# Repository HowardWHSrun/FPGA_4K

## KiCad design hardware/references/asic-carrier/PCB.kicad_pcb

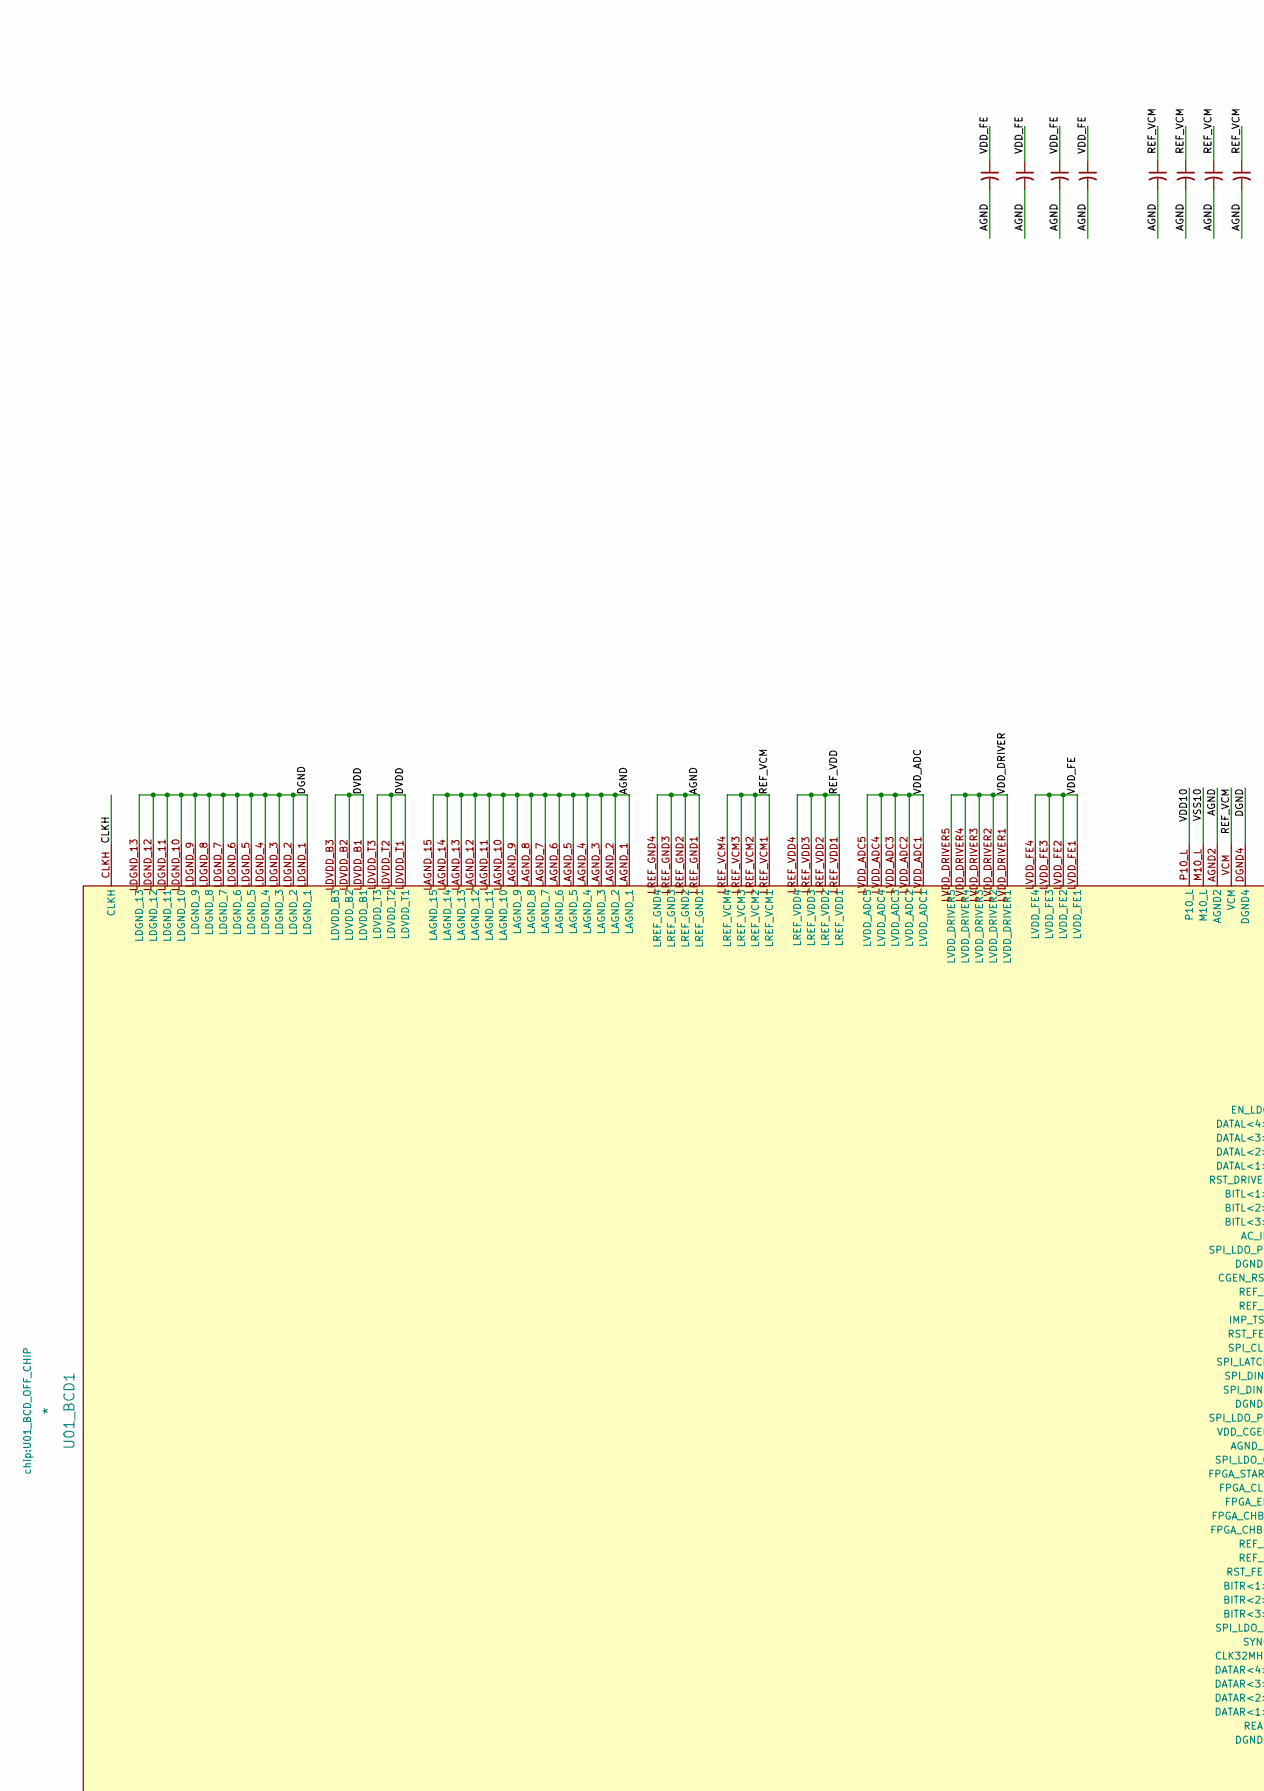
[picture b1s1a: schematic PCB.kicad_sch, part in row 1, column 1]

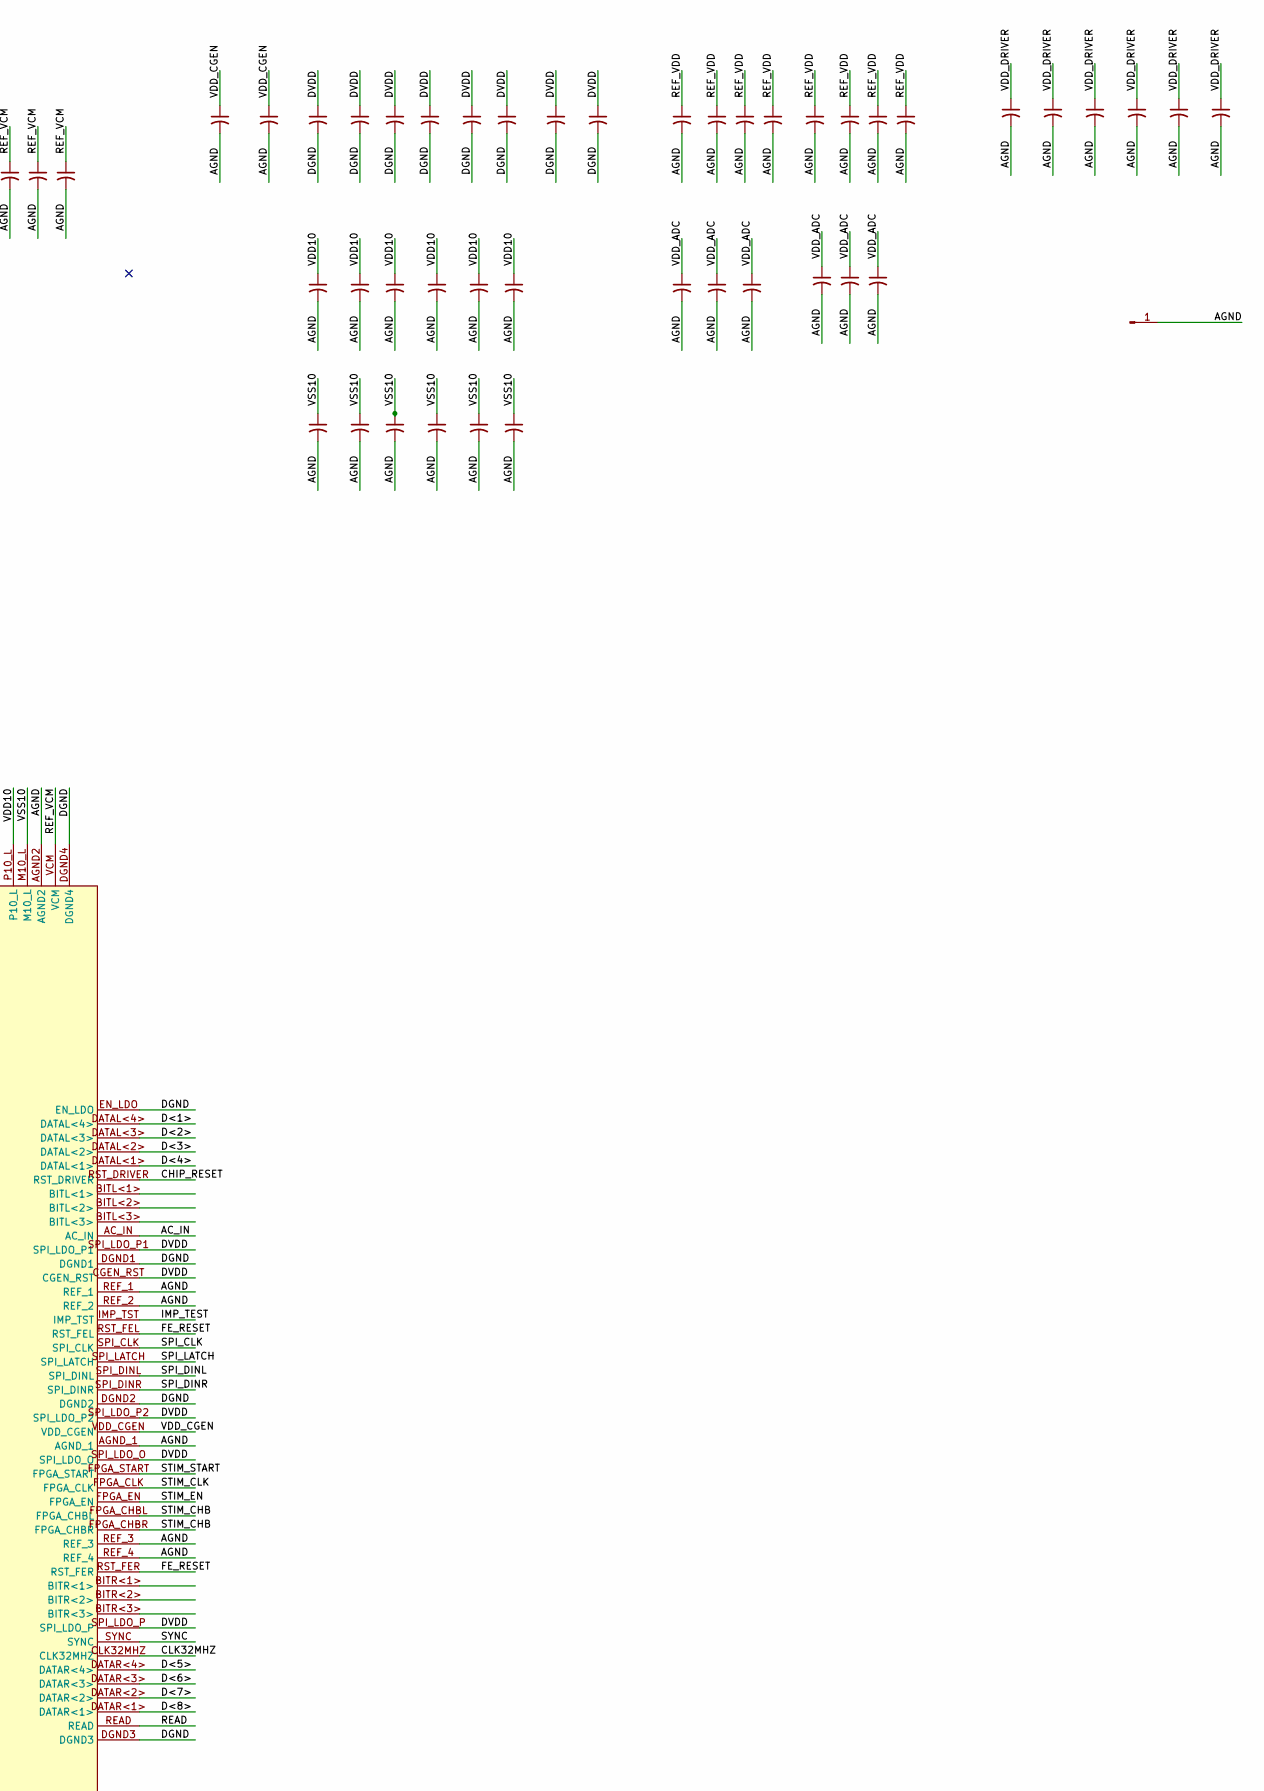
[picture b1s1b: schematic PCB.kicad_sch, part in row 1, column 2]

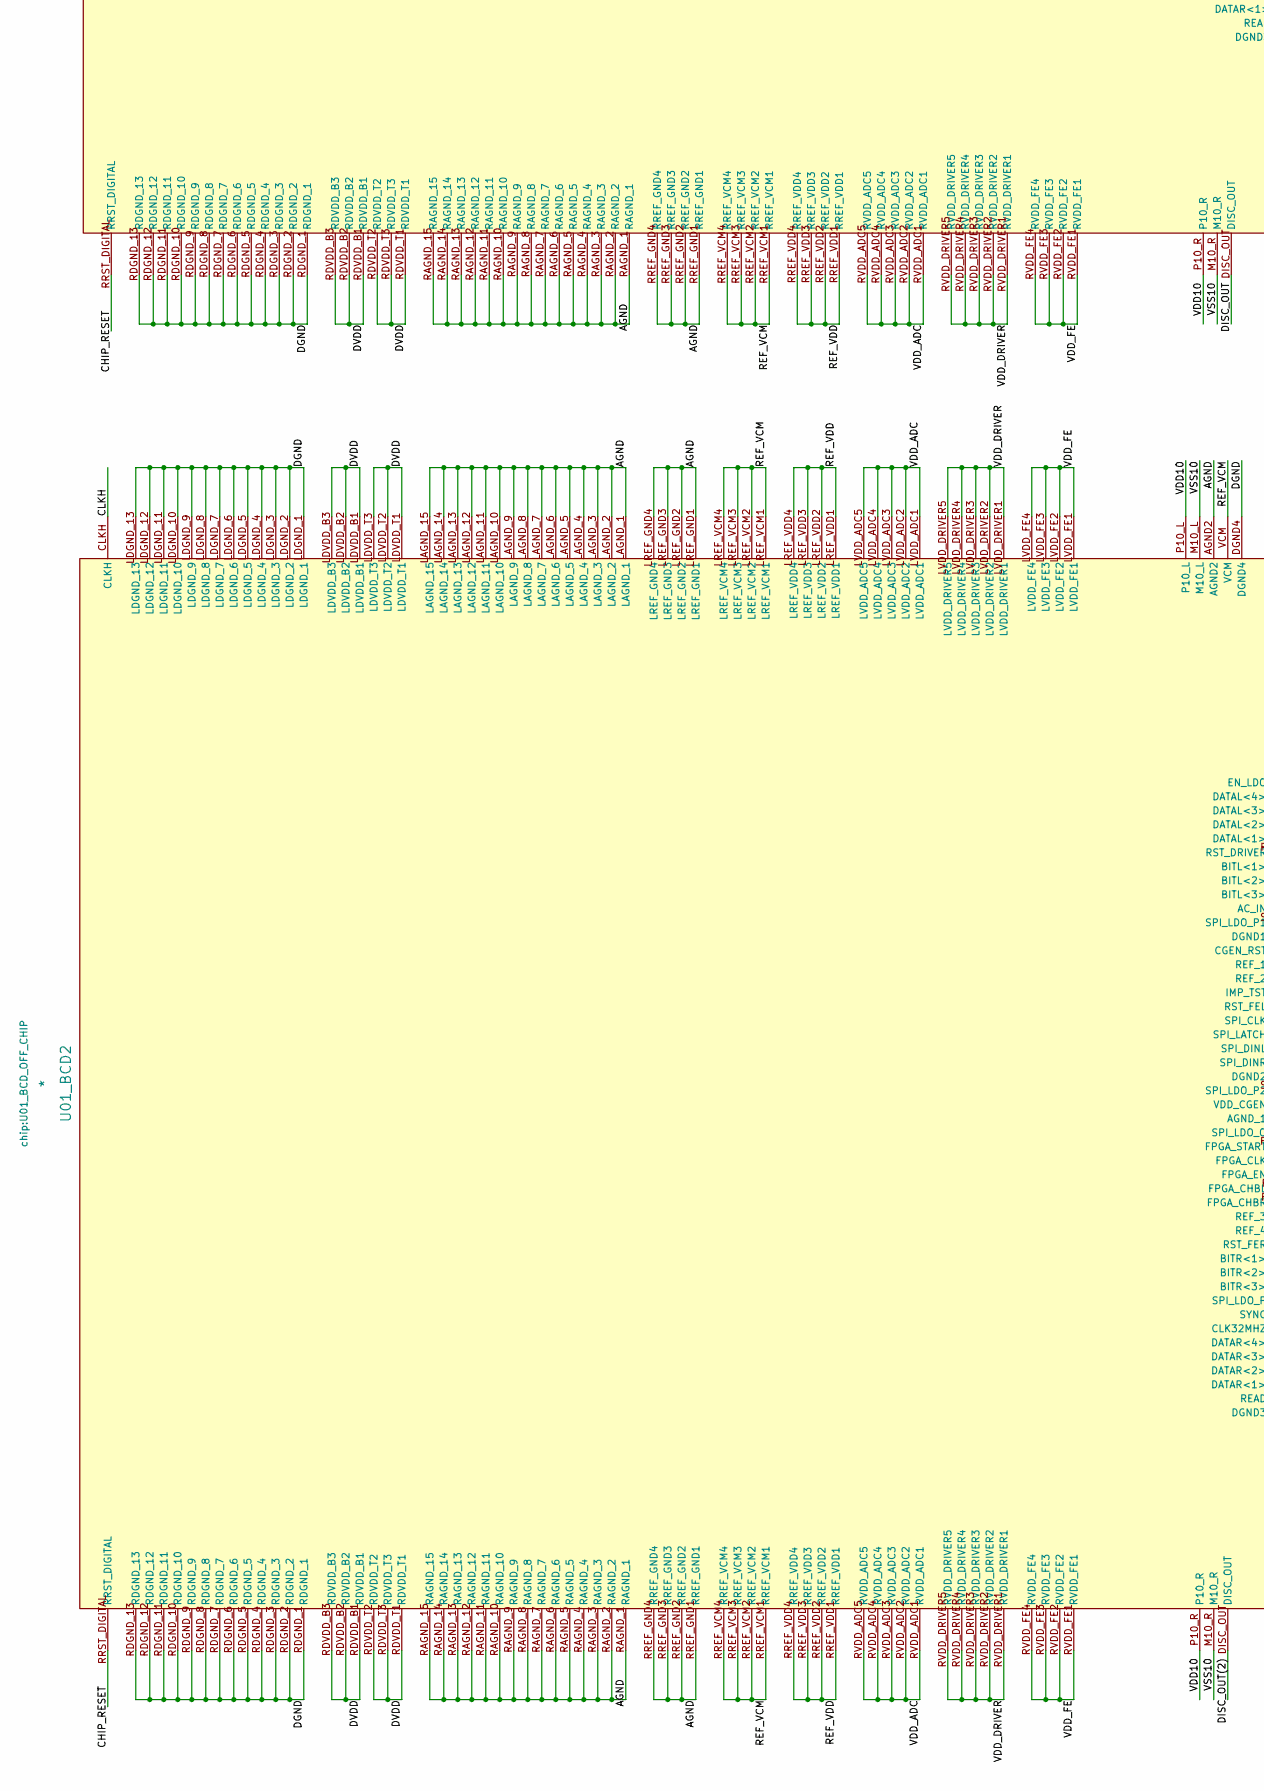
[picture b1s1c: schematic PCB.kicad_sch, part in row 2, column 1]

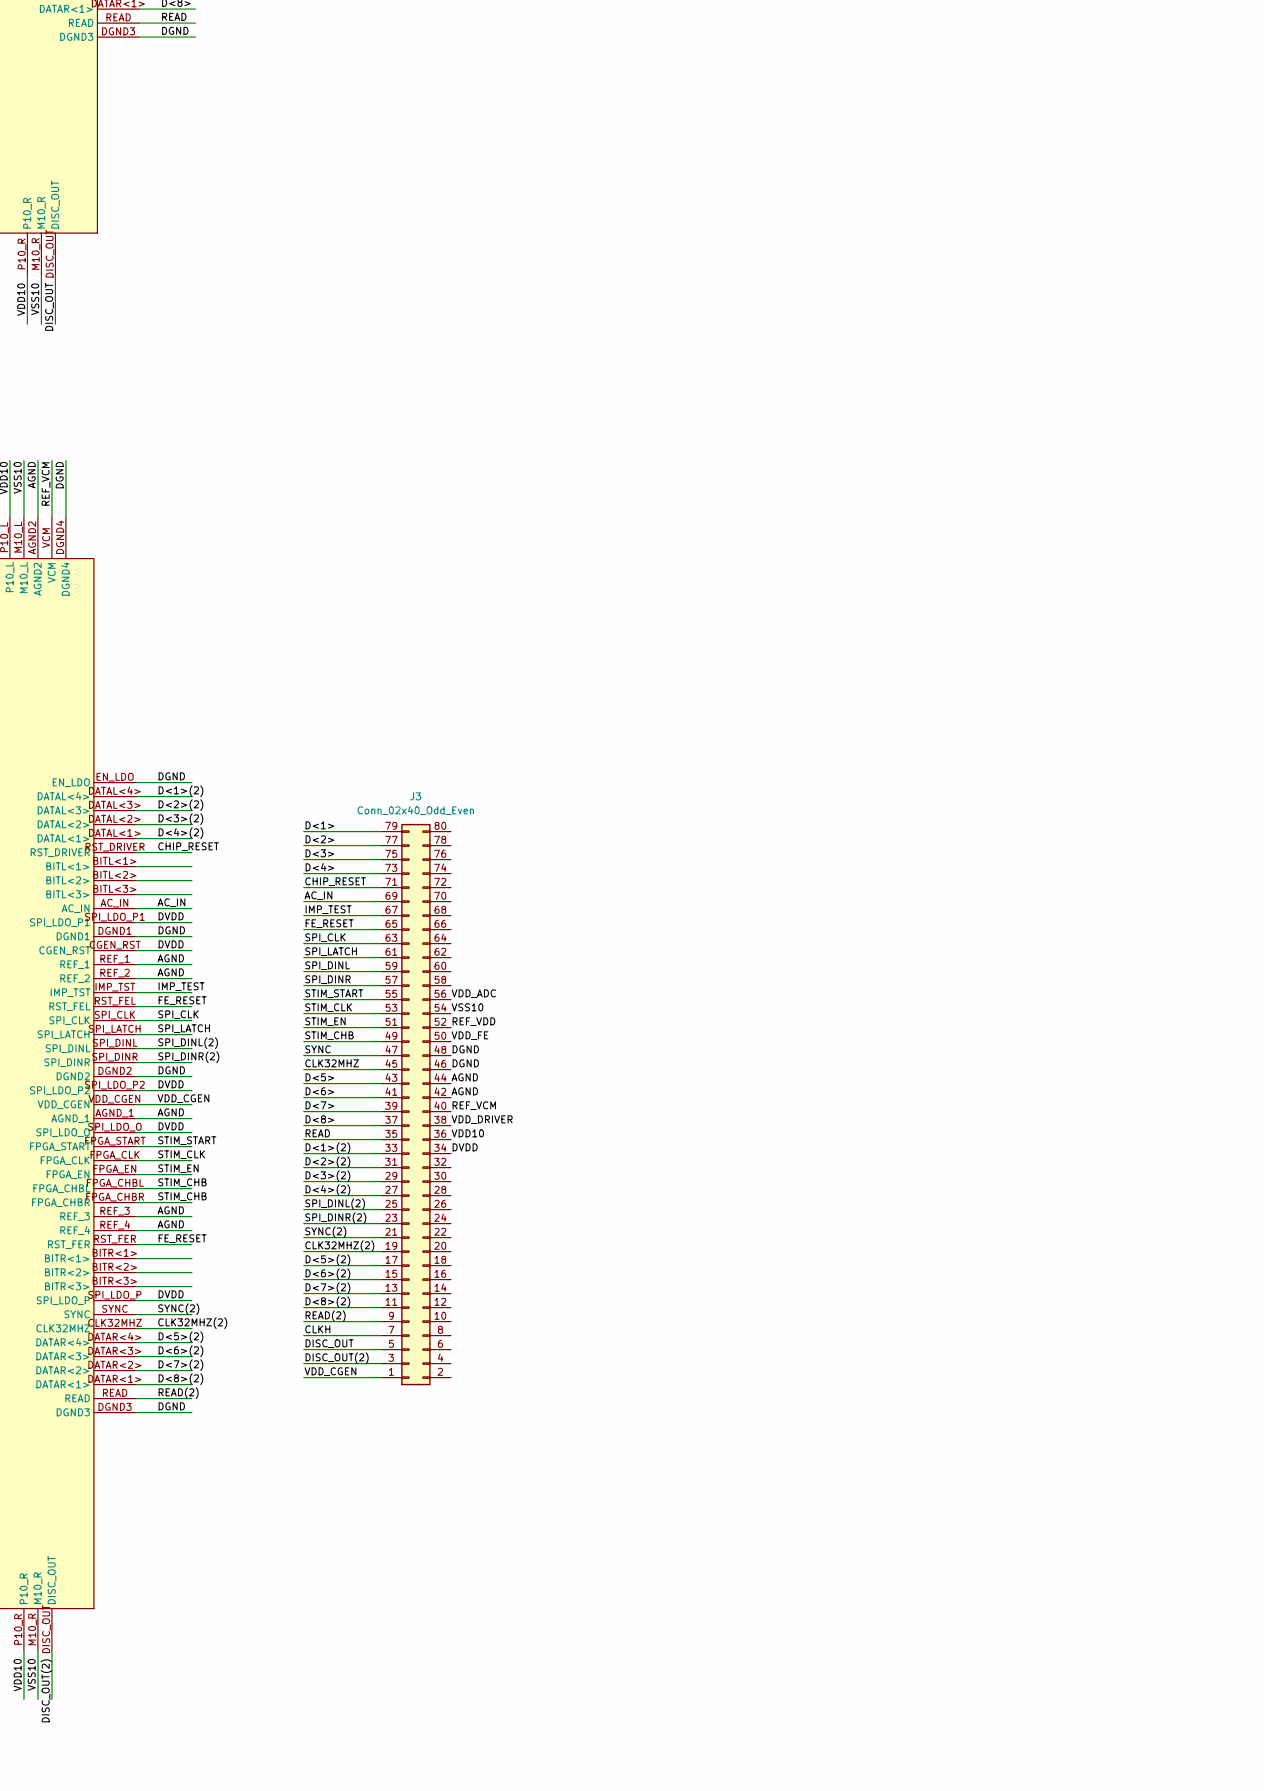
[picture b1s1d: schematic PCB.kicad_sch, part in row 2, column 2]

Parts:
C1, C2, C3, C4, C5, C6, C7, C8, C9, C10, C11, C12, C13, C14, C15, C16, C17, C18, C19, C20, C21, C22, C23, C24, C25, C26, C27, C28, C29, C30, C31, C32, C33, C34, C35, C36, C37, C38, C39, C40, C41, C42, C43, C44, C45, C46, C47, C48, C49, C50: C_Small_US; C_0201_0603Metric
J1: Conn_01x01_Pin; PinHeader_1x01_P1.00mm_Horizontal
J3: Conn_02x40_Odd_Even; Hirose_DF40C-80DS-0.4V_2x40_P0.4mm
U01_BCD1, U01_BCD2: *; U01_BCD_OFF_CHIP

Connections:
/AC_IN: J3.69, U01_BCD1.AC_IN, U01_BCD2.AC_IN
/AGND: C1.2, C2.2, C3.2, C4.2, C5.2, C6.2, C15.2, C16.2, C17.2, C18.2, C19.2, C20.2, C21.2, C22.2, C23.2, C24.2, C25.2, C26.2, C27.2, C28.2, C29.2, C30.2, C31.2, C32.2, C33.2, C34.2, C35.2, C36.2, C37.2, C38.2, C39.2, C40.2, C41.2, C42.2, C43.2, C44.2, C45.2, C46.2, C47.2, C48.2, C49.2, C50.2, J1.1 (Pin_1_1), J3.42, J3.44, U01_BCD1.AGND2, U01_BCD1.AGND_1, U01_BCD1.LAGND_1, U01_BCD1.LAGND_2, U01_BCD1.LAGND_3, U01_BCD1.LAGND_4, U01_BCD1.LAGND_5, U01_BCD1.LAGND_6, U01_BCD1.LAGND_7, U01_BCD1.LAGND_8, U01_BCD1.LAGND_9, U01_BCD1.LAGND_10, U01_BCD1.LAGND_11, U01_BCD1.LAGND_12, U01_BCD1.LAGND_13, U01_BCD1.LAGND_14, U01_BCD1.LAGND_15, U01_BCD1.LREF_GND1, U01_BCD1.LREF_GND2, U01_BCD1.LREF_GND3, U01_BCD1.LREF_GND4, U01_BCD1.RAGND_1, U01_BCD1.RAGND_2, U01_BCD1.RAGND_3, U01_BCD1.RAGND_4, U01_BCD1.RAGND_5, U01_BCD1.RAGND_6, U01_BCD1.RAGND_7, U01_BCD1.RAGND_8, U01_BCD1.RAGND_9, U01_BCD1.RAGND_10, U01_BCD1.RAGND_11, U01_BCD1.RAGND_12, U01_BCD1.RAGND_13, U01_BCD1.RAGND_14, U01_BCD1.RAGND_15, U01_BCD1.REF_1, U01_BCD1.REF_2, U01_BCD1.REF_3, U01_BCD1.REF_4, U01_BCD1.RREF_GND1, U01_BCD1.RREF_GND2, U01_BCD1.RREF_GND3, U01_BCD1.RREF_GND4, U01_BCD2.AGND2, U01_BCD2.AGND_1, U01_BCD2.LAGND_1, U01_BCD2.LAGND_2, U01_BCD2.LAGND_3, U01_BCD2.LAGND_4, U01_BCD2.LAGND_5, U01_BCD2.LAGND_6, U01_BCD2.LAGND_7, U01_BCD2.LAGND_8, U01_BCD2.LAGND_9, U01_BCD2.LAGND_10, U01_BCD2.LAGND_11, U01_BCD2.LAGND_12, U01_BCD2.LAGND_13, U01_BCD2.LAGND_14, U01_BCD2.LAGND_15, U01_BCD2.LREF_GND1, U01_BCD2.LREF_GND2, U01_BCD2.LREF_GND3, U01_BCD2.LREF_GND4, U01_BCD2.RAGND_1, U01_BCD2.RAGND_2, U01_BCD2.RAGND_3, U01_BCD2.RAGND_4, U01_BCD2.RAGND_5, U01_BCD2.RAGND_6, U01_BCD2.RAGND_7, U01_BCD2.RAGND_8, U01_BCD2.RAGND_9, U01_BCD2.RAGND_10, U01_BCD2.RAGND_11, U01_BCD2.RAGND_12, U01_BCD2.RAGND_13, U01_BCD2.RAGND_14, U01_BCD2.RAGND_15, U01_BCD2.REF_1, U01_BCD2.REF_2, U01_BCD2.REF_3, U01_BCD2.REF_4, U01_BCD2.RREF_GND1, U01_BCD2.RREF_GND2, U01_BCD2.RREF_GND3, U01_BCD2.RREF_GND4
/CHIP_RESET: J3.71, U01_BCD1.RRST_DIGITAL, U01_BCD1.RST_DRIVER, U01_BCD2.RRST_DIGITAL, U01_BCD2.RST_DRIVER
/CLK32MHZ: J3.45, U01_BCD1.CLK32MHZ
/CLK32MHZ(2): J3.19, U01_BCD2.CLK32MHZ
/CLKH: J3.7, U01_BCD1.CLKH, U01_BCD2.CLKH
/D<1>: J3.79, U01_BCD1.DATAL<4>
/D<1>(2): J3.33, U01_BCD2.DATAL<4>
/D<2>: J3.77, U01_BCD1.DATAL<3>
/D<2>(2): J3.31, U01_BCD2.DATAL<3>
/D<3>: J3.75, U01_BCD1.DATAL<2>
/D<3>(2): J3.29, U01_BCD2.DATAL<2>
/D<4>: J3.73, U01_BCD1.DATAL<1>
/D<4>(2): J3.27, U01_BCD2.DATAL<1>
/D<5>: J3.43, U01_BCD1.DATAR<4>
/D<5>(2): J3.17, U01_BCD2.DATAR<4>
/D<6>: J3.41, U01_BCD1.DATAR<3>
/D<6>(2): J3.15, U01_BCD2.DATAR<3>
/D<7>: J3.39, U01_BCD1.DATAR<2>
/D<7>(2): J3.13, U01_BCD2.DATAR<2>
/D<8>: J3.37, U01_BCD1.DATAR<1>
/D<8>(2): J3.11, U01_BCD2.DATAR<1>
/DGND: C7.2, C8.2, C9.2, C10.2, C11.2, C12.2, C13.2, C14.2, J3.46, J3.48, U01_BCD1.DGND1, U01_BCD1.DGND2, U01_BCD1.DGND3, U01_BCD1.DGND4, U01_BCD1.EN_LDO, U01_BCD1.LDGND_1, U01_BCD1.LDGND_2, U01_BCD1.LDGND_3, U01_BCD1.LDGND_4, U01_BCD1.LDGND_5, U01_BCD1.LDGND_6, U01_BCD1.LDGND_7, U01_BCD1.LDGND_8, U01_BCD1.LDGND_9, U01_BCD1.LDGND_10, U01_BCD1.LDGND_11, U01_BCD1.LDGND_12, U01_BCD1.LDGND_13, U01_BCD1.RDGND_1, U01_BCD1.RDGND_2, U01_BCD1.RDGND_3, U01_BCD1.RDGND_4, U01_BCD1.RDGND_5, U01_BCD1.RDGND_6, U01_BCD1.RDGND_7, U01_BCD1.RDGND_8, U01_BCD1.RDGND_9, U01_BCD1.RDGND_10, U01_BCD1.RDGND_11, U01_BCD1.RDGND_12, U01_BCD1.RDGND_13, U01_BCD2.DGND1, U01_BCD2.DGND2, U01_BCD2.DGND3, U01_BCD2.DGND4, U01_BCD2.EN_LDO, U01_BCD2.LDGND_1, U01_BCD2.LDGND_2, U01_BCD2.LDGND_3, U01_BCD2.LDGND_4, U01_BCD2.LDGND_5, U01_BCD2.LDGND_6, U01_BCD2.LDGND_7, U01_BCD2.LDGND_8, U01_BCD2.LDGND_9, U01_BCD2.LDGND_10, U01_BCD2.LDGND_11, U01_BCD2.LDGND_12, U01_BCD2.LDGND_13, U01_BCD2.RDGND_1, U01_BCD2.RDGND_2, U01_BCD2.RDGND_3, U01_BCD2.RDGND_4, U01_BCD2.RDGND_5, U01_BCD2.RDGND_6, U01_BCD2.RDGND_7, U01_BCD2.RDGND_8, U01_BCD2.RDGND_9, U01_BCD2.RDGND_10, U01_BCD2.RDGND_11, U01_BCD2.RDGND_12, U01_BCD2.RDGND_13
/DISC_OUT: J3.5, U01_BCD1.DISC_OUT
/DISC_OUT(2): J3.3, U01_BCD2.DISC_OUT
/DVDD: C7.1, C8.1, C9.1, C10.1, C11.1, C12.1, C13.1, C14.1, J3.34, U01_BCD1.CGEN_RST, U01_BCD1.LDVDD_B1, U01_BCD1.LDVDD_B2, U01_BCD1.LDVDD_B3, U01_BCD1.LDVDD_T1, U01_BCD1.LDVDD_T2, U01_BCD1.LDVDD_T3, U01_BCD1.RDVDD_B1, U01_BCD1.RDVDD_B2, U01_BCD1.RDVDD_B3, U01_BCD1.RDVDD_T1, U01_BCD1.RDVDD_T2, U01_BCD1.RDVDD_T3, U01_BCD1.SPI_LDO_O, U01_BCD1.SPI_LDO_P, U01_BCD1.SPI_LDO_P1, U01_BCD1.SPI_LDO_P2, U01_BCD2.CGEN_RST, U01_BCD2.LDVDD_B1, U01_BCD2.LDVDD_B2, U01_BCD2.LDVDD_B3, U01_BCD2.LDVDD_T1, U01_BCD2.LDVDD_T2, U01_BCD2.LDVDD_T3, U01_BCD2.RDVDD_B1, U01_BCD2.RDVDD_B2, U01_BCD2.RDVDD_B3, U01_BCD2.RDVDD_T1, U01_BCD2.RDVDD_T2, U01_BCD2.RDVDD_T3, U01_BCD2.SPI_LDO_O, U01_BCD2.SPI_LDO_P, U01_BCD2.SPI_LDO_P1, U01_BCD2.SPI_LDO_P2
/FE_RESET: J3.65, U01_BCD1.RST_FEL, U01_BCD1.RST_FER, U01_BCD2.RST_FEL, U01_BCD2.RST_FER
/IMP_TEST: J3.67, U01_BCD1.IMP_TST, U01_BCD2.IMP_TST
/READ: J3.35, U01_BCD1.READ
/READ(2): J3.9, U01_BCD2.READ
/REF_VCM: C5.1, C46.1, C47.1, C49.1, J3.40, U01_BCD1.LREF_VCM1, U01_BCD1.LREF_VCM2, U01_BCD1.LREF_VCM3, U01_BCD1.LREF_VCM4, U01_BCD1.RREF_VCM1, U01_BCD1.RREF_VCM2, U01_BCD1.RREF_VCM3, U01_BCD1.RREF_VCM4, U01_BCD1.VCM, U01_BCD2.LREF_VCM1, U01_BCD2.LREF_VCM2, U01_BCD2.LREF_VCM3, U01_BCD2.LREF_VCM4, U01_BCD2.RREF_VCM1, U01_BCD2.RREF_VCM2, U01_BCD2.RREF_VCM3, U01_BCD2.RREF_VCM4, U01_BCD2.VCM
/REF_VDD: C2.1, C27.1, C28.1, C29.1, C30.1, C31.1, C32.1, C33.1, J3.52, U01_BCD1.LREF_VDD1, U01_BCD1.LREF_VDD2, U01_BCD1.LREF_VDD3, U01_BCD1.LREF_VDD4, U01_BCD1.RREF_VDD1, U01_BCD1.RREF_VDD2, U01_BCD1.RREF_VDD3, U01_BCD1.RREF_VDD4, U01_BCD2.LREF_VDD1, U01_BCD2.LREF_VDD2, U01_BCD2.LREF_VDD3, U01_BCD2.LREF_VDD4, U01_BCD2.RREF_VDD1, U01_BCD2.RREF_VDD2, U01_BCD2.RREF_VDD3, U01_BCD2.RREF_VDD4
/SPI_CLK: J3.63, U01_BCD1.SPI_CLK, U01_BCD2.SPI_CLK
/SPI_DINL: J3.59, U01_BCD1.SPI_DINL
/SPI_DINL(2): J3.25, U01_BCD2.SPI_DINL
/SPI_DINR: J3.57, U01_BCD1.SPI_DINR
/SPI_DINR(2): J3.23, U01_BCD2.SPI_DINR
/SPI_LATCH: J3.61, U01_BCD1.SPI_LATCH, U01_BCD2.SPI_LATCH
/STIM_CHB: J3.49, U01_BCD1.FPGA_CHBL, U01_BCD1.FPGA_CHBR, U01_BCD2.FPGA_CHBL, U01_BCD2.FPGA_CHBR
/STIM_CLK: J3.53, U01_BCD1.FPGA_CLK, U01_BCD2.FPGA_CLK
/STIM_EN: J3.51, U01_BCD1.FPGA_EN, U01_BCD2.FPGA_EN
/STIM_START: J3.55, U01_BCD1.FPGA_START, U01_BCD2.FPGA_START
/SYNC: J3.47, U01_BCD1.SYNC
/SYNC(2): J3.21, U01_BCD2.SYNC
/VDD10: C15.1, C16.1, C17.1, C18.1, C19.1, C20.1, J3.36, U01_BCD1.P10_L, U01_BCD1.P10_R, U01_BCD2.P10_L, U01_BCD2.P10_R
/VDD_ADC: C1.1, C34.1, C35.1, C36.1, C37.1, C38.1, J3.56, U01_BCD1.LVDD_ADC1, U01_BCD1.LVDD_ADC2, U01_BCD1.LVDD_ADC3, U01_BCD1.LVDD_ADC4, U01_BCD1.LVDD_ADC5, U01_BCD1.RVDD_ADC1, U01_BCD1.RVDD_ADC2, U01_BCD1.RVDD_ADC3, U01_BCD1.RVDD_ADC4, U01_BCD1.RVDD_ADC5, U01_BCD2.LVDD_ADC1, U01_BCD2.LVDD_ADC2, U01_BCD2.LVDD_ADC3, U01_BCD2.LVDD_ADC4, U01_BCD2.LVDD_ADC5, U01_BCD2.RVDD_ADC1, U01_BCD2.RVDD_ADC2, U01_BCD2.RVDD_ADC3, U01_BCD2.RVDD_ADC4, U01_BCD2.RVDD_ADC5
/VDD_CGEN: C6.1, C50.1, J3.1, U01_BCD1.VDD_CGEN, U01_BCD2.VDD_CGEN
/VDD_DRIVER: C3.1, C39.1, C40.1, C41.1, C42.1, C43.1, J3.38, U01_BCD1.LVDD_DRIVER1, U01_BCD1.LVDD_DRIVER2, U01_BCD1.LVDD_DRIVER3, U01_BCD1.LVDD_DRIVER4, U01_BCD1.LVDD_DRIVER5, U01_BCD1.RVDD_DRIVER1, U01_BCD1.RVDD_DRIVER2, U01_BCD1.RVDD_DRIVER3, U01_BCD1.RVDD_DRIVER4, U01_BCD1.RVDD_DRIVER5, U01_BCD2.LVDD_DRIVER1, U01_BCD2.LVDD_DRIVER2, U01_BCD2.LVDD_DRIVER3, U01_BCD2.LVDD_DRIVER4, U01_BCD2.LVDD_DRIVER5, U01_BCD2.RVDD_DRIVER1, U01_BCD2.RVDD_DRIVER2, U01_BCD2.RVDD_DRIVER3, U01_BCD2.RVDD_DRIVER4, U01_BCD2.RVDD_DRIVER5
/VDD_FE: C4.1, C44.1, C45.1, C48.1, J3.50, U01_BCD1.LVDD_FE1, U01_BCD1.LVDD_FE2, U01_BCD1.LVDD_FE3, U01_BCD1.LVDD_FE4, U01_BCD1.RVDD_FE1, U01_BCD1.RVDD_FE2, U01_BCD1.RVDD_FE3, U01_BCD1.RVDD_FE4, U01_BCD2.LVDD_FE1, U01_BCD2.LVDD_FE2, U01_BCD2.LVDD_FE3, U01_BCD2.LVDD_FE4, U01_BCD2.RVDD_FE1, U01_BCD2.RVDD_FE2, U01_BCD2.RVDD_FE3, U01_BCD2.RVDD_FE4
/VSS10: C21.1, C22.1, C23.1, C24.1, C25.1, C26.1, J3.54, U01_BCD1.M10_L, U01_BCD1.M10_R, U01_BCD2.M10_L, U01_BCD2.M10_R

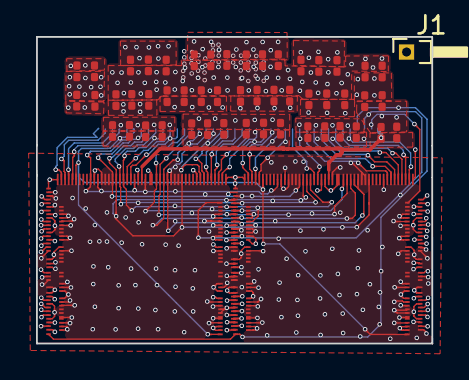
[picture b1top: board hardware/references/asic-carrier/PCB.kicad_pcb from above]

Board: 10 copper layers, 22.0 x 17.0 mm, 54 parts (1 on the bottom side), 50 nets.

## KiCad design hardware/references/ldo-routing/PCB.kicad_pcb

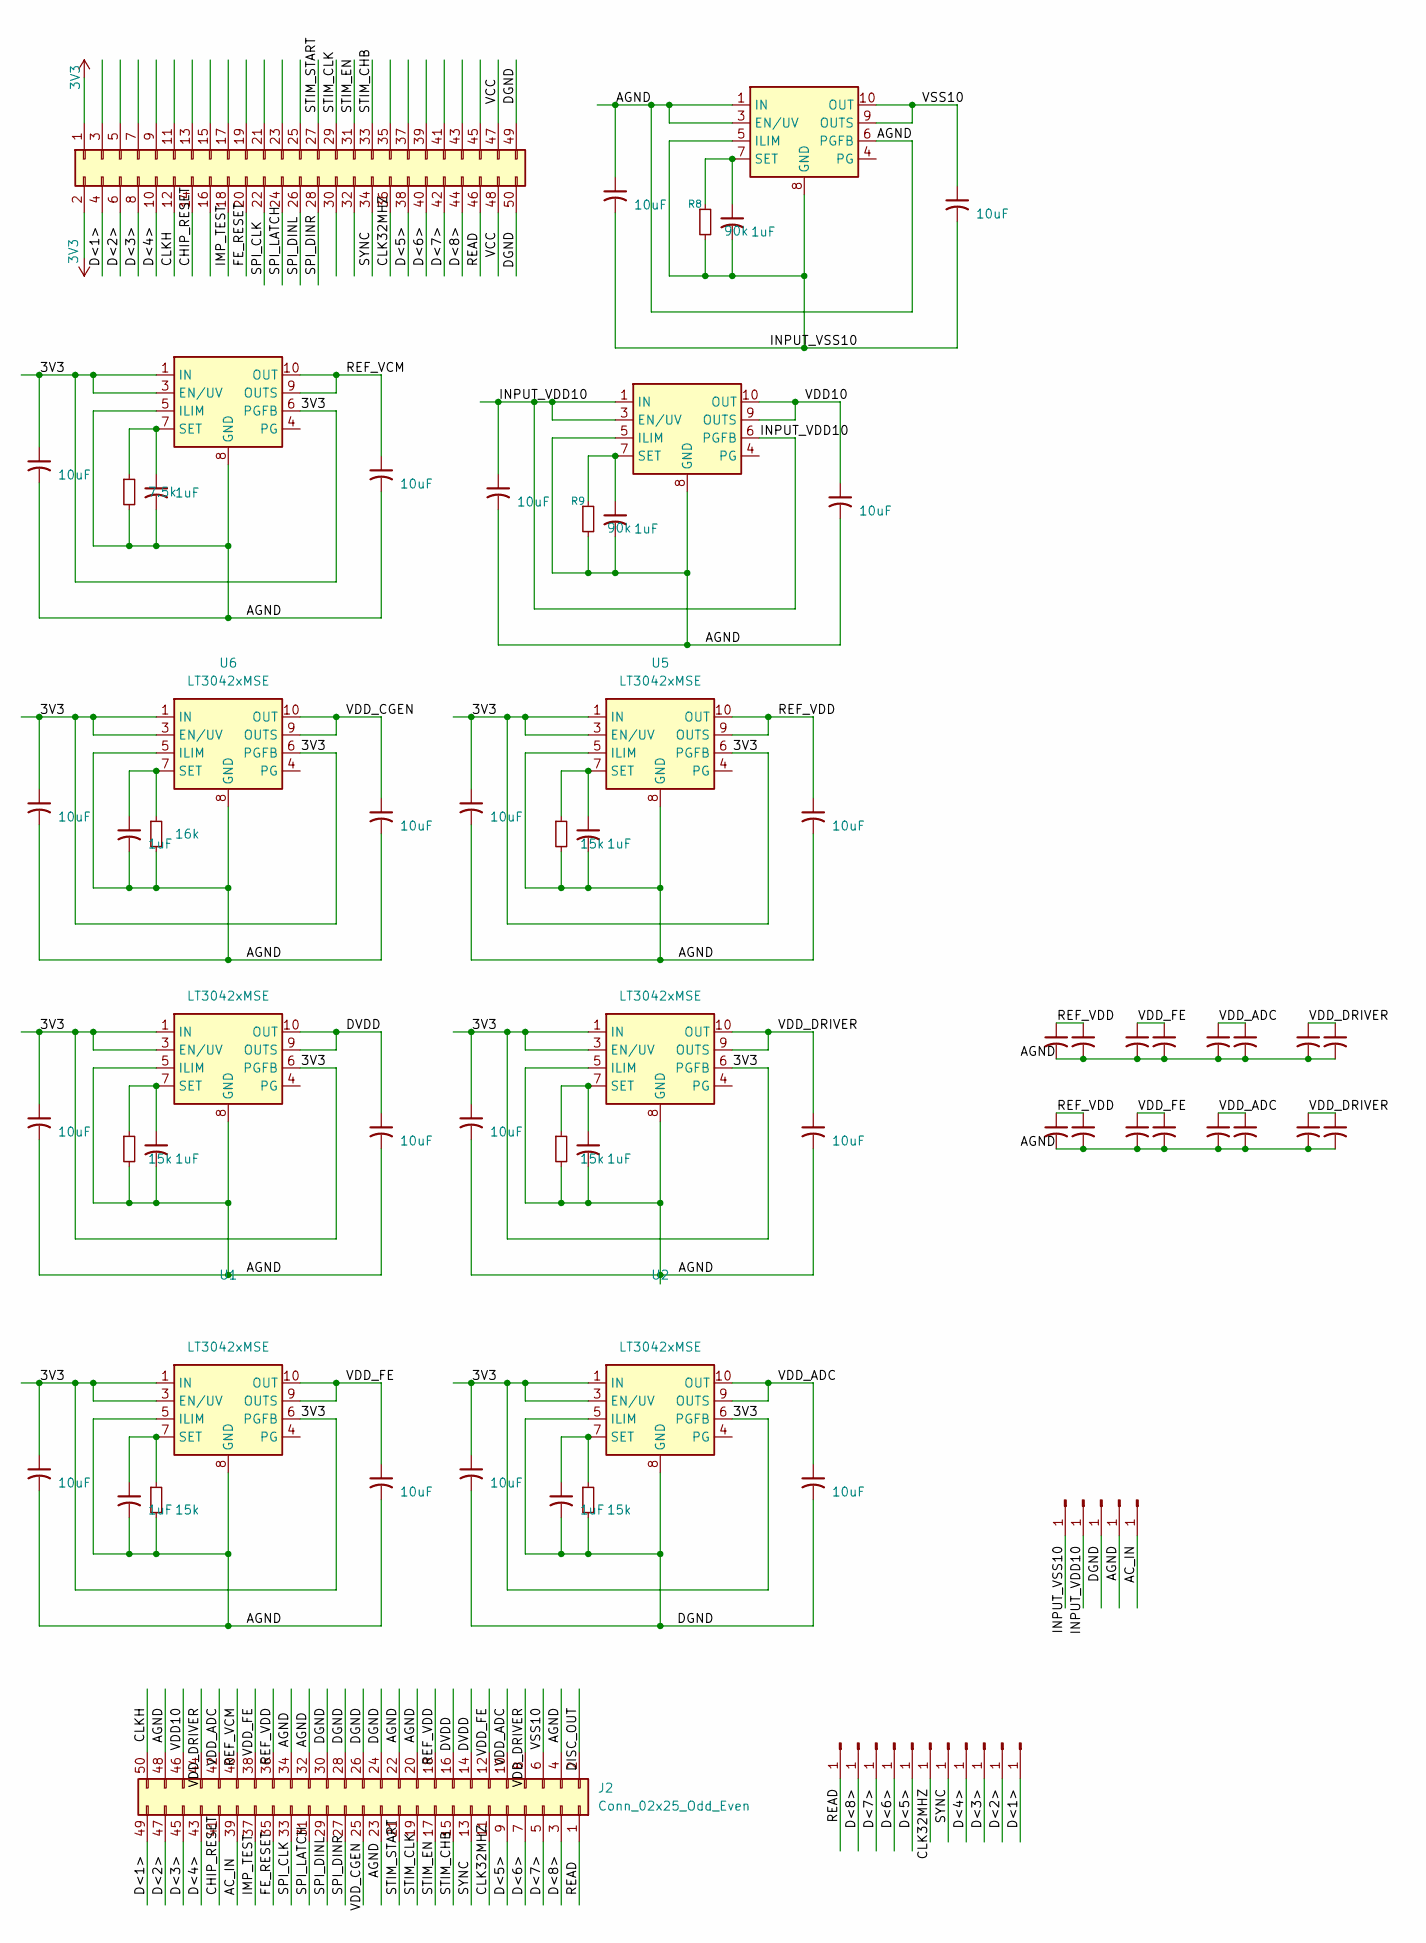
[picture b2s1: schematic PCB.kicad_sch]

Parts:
C1, C6, C7, C11, C15, C18, C19, C22, C27: 1uF; C_0603_1608Metric
C2, C3, C4, C5, C8, C9, C10, C12, C13, C14, C16, C17, C20, C21, C23, C24, C25, C28: 10uF; C_0603_1608Metric
C26, C29, C30, C31, C32, C33, C34, C35, C36, C37, C38, C39, C40, C41, C42, C43: 10uF; C_0201_0603Metric
J1: Conn_02x25_Odd_Even; Hirose_DF40C-50DP-0.4V_2x25-1MP_P0.4mm
J2: Conn_02x25_Odd_Even; HRS_DF40C-50DS-0.4V(Correct Orientation)
J3, J4, J5, J6, J7, J8, J9, J10, J11, J12, J13, J14, J15, J16, J17, J18: Conn_01x01_Pin; PinHeader_1x01_P1.00mm_Horizontal
R1: 7.5k; C_0603_1608Metric
R2: 16k; C_0603_1608Metric
R3, R4, R5, R6, R7: 15k; C_0603_1608Metric
R8, R9: 90k; C_0603_1608Metric
U1, U2, U3, U4, U5, U6, U7, U8, U9: LT3042xMSE; DFN-10-1EP_3x3mm_P0.5mm_EP1.65x2.38mm

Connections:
3V3: C3.1, C5.1, C9.1, C13.1, C17.1, C21.1, C25.1, J1.1, J1.2, U1.1 (IN), U1.2 (IN), U1.3 (EN/UV), U1.6 (PGFB), U2.1 (IN), U2.2 (IN), U2.3 (EN/UV), U2.6 (PGFB), U3.1 (IN), U3.2 (IN), U3.3 (EN/UV), U3.6 (PGFB), U4.1 (IN), U4.2 (IN), U4.3 (EN/UV), U4.6 (PGFB), U5.1 (IN), U5.2 (IN), U5.3 (EN/UV), U5.6 (PGFB), U6.1 (IN), U6.2 (IN), U6.3 (EN/UV), U6.6 (PGFB), U7.1 (IN), U7.2 (IN), U7.3 (EN/UV), U7.6 (PGFB)
/AC_IN: J2.39, J18.1
/AGND: C1.2, C2.2, C3.2, C4.2, C7.2, C9.2, C10.2, C11.2, C12.2, C13.2, C14.1, C15.2, C16.2, C17.2, C19.2, C20.2, C21.2, C22.2, C24.2, C25.2, C26.2, C27.2, C28.2, C29.2, C30.2, C31.2, C32.2, C33.2, C34.2, C35.2, C36.2, C37.2, C38.2, C39.2, C40.2, C41.2, C42.2, C43.2, J2.4, J2.20, J2.22, J2.23, J2.32, J2.34, J2.48, J17.1, R1.2, R2.2, R3.2, R4.2, R6.2, R7.2, R9.2, U1.5 (ILIM), U1.8 (GND), U1.11 (GND), U3.5 (ILIM), U3.8 (GND), U3.11 (GND), U4.5 (ILIM), U4.8 (GND), U4.11 (GND), U5.5 (ILIM), U5.8 (GND), U5.11 (GND), U6.5 (ILIM), U6.8 (GND), U6.11 (GND), U7.5 (ILIM), U7.8 (GND), U7.11 (GND), U8.5 (ILIM), U8.8 (GND), U8.11 (GND), U9.1 (IN), U9.2 (IN), U9.3 (EN/UV), U9.6 (PGFB)
/CHIP_RESET: J1.14, J2.41
/CLK32MHZ: J1.36, J2.11, J14.1
/CLKH: J1.12, J2.50
/D<1>: J1.4, J2.49, J9.1
/D<2>: J1.6, J2.47, J10.1
/D<3>: J1.8, J2.45, J11.1
/D<4>: J1.10, J2.43, J12.1
/D<5>: J1.38, J2.9, J3.1
/D<6>: J1.40, J2.7, J4.1
/D<7>: J1.42, J2.5, J5.1
/D<8>: J1.44, J2.3, J6.1
/DGND: C5.2, C6.2, C8.2, J1.49, J1.50, J2.24, J2.26, J2.28, J2.30, J16.1, R5.2, U2.5 (ILIM), U2.8 (GND), U2.11 (GND)
/DISC_OUT: J2.2
/DVDD: C16.1, J2.14, J2.16, U4.9 (OUTS), U4.10 (OUT)
/FE_RESET: J1.20, J2.35
/IMP_TEST: J1.18, J2.37
/INPUT_VDD10: C2.1, J15.1, U8.1 (IN), U8.2 (IN), U8.3 (EN/UV), U8.6 (PGFB)
/INPUT_VSS10: C14.2, C18.2, C23.2, J8.1, R8.2, U9.5 (ILIM), U9.8 (GND), U9.11 (GND)
/READ: J1.46, J2.1, J7.1
/REF_VCM: C28.1, J2.40, U7.9 (OUTS), U7.10 (OUT)
/REF_VDD: C20.1, C26.1, C33.1, C42.1, C43.1, J2.18, J2.36, U5.9 (OUTS), U5.10 (OUT)
/SPI_CLK: J1.22, J2.33
/SPI_DINL: J1.26, J2.29
/SPI_DINR: J1.28, J2.27
/SPI_LATCH: J1.24, J2.31
/STIM_CHB: J1.33, J2.15
/STIM_CLK: J1.29, J2.19
/STIM_EN: J1.31, J2.17
/STIM_START: J1.27, J2.21
/SYNC: J1.34, J2.13, J13.1
/VCC: J1.47, J1.48
/VDD10: C10.1, J2.46, U8.9 (OUTS), U8.10 (OUT)
/VDD_ADC: C8.1, C31.1, C32.1, C38.1, C39.1, J2.10, J2.42, U2.9 (OUTS), U2.10 (OUT)
/VDD_CGEN: C24.1, J2.25, U6.9 (OUTS), U6.10 (OUT)
/VDD_DRIVER: C12.1, C34.1, C35.1, C36.1, C37.1, J2.8, J2.44, U3.9 (OUTS), U3.10 (OUT)
/VDD_FE: C4.1, C29.1, C30.1, C40.1, C41.1, J2.12, J2.38, U1.9 (OUTS), U1.10 (OUT)
/VSS10: C23.1, J2.6, U9.9 (OUTS), U9.10 (OUT)
unnamed: C1.1, R4.1, U1.7 (SET)
unnamed: C6.1, R5.1, U2.7 (SET)
unnamed: C11.1, R6.1, U3.7 (SET)
unnamed: C15.1, R3.1, U4.7 (SET)
unnamed: C19.1, R7.1, U5.7 (SET)
unnamed: C22.1, R2.1, U6.7 (SET)
unnamed: C27.1, R1.1, U7.7 (SET)
unnamed: C7.1, R9.1, U8.7 (SET)
unnamed: C18.1, R8.1, U9.7 (SET)

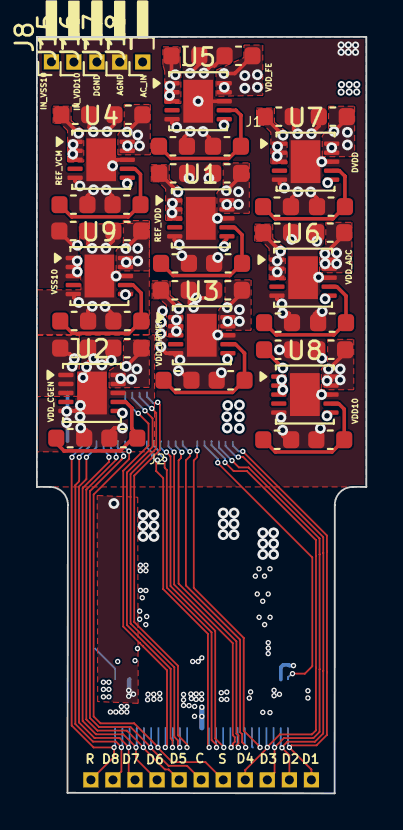
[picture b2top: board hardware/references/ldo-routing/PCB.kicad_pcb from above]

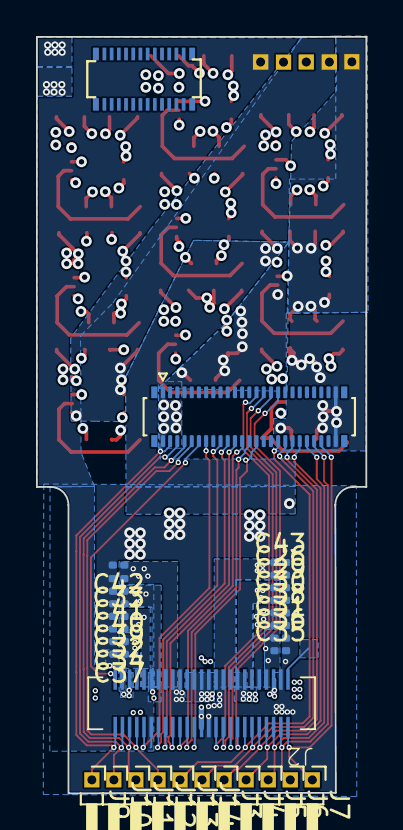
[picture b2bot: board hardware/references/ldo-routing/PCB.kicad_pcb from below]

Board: 6 copper layers, 18.3 x 42.0 mm, 80 parts (30 on the bottom side), 48 nets.

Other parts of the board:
J1#2: DF40C-24DP
